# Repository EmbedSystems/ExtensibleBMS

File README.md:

# BMS
An extensible BMS with fast charging and battery pack scalability

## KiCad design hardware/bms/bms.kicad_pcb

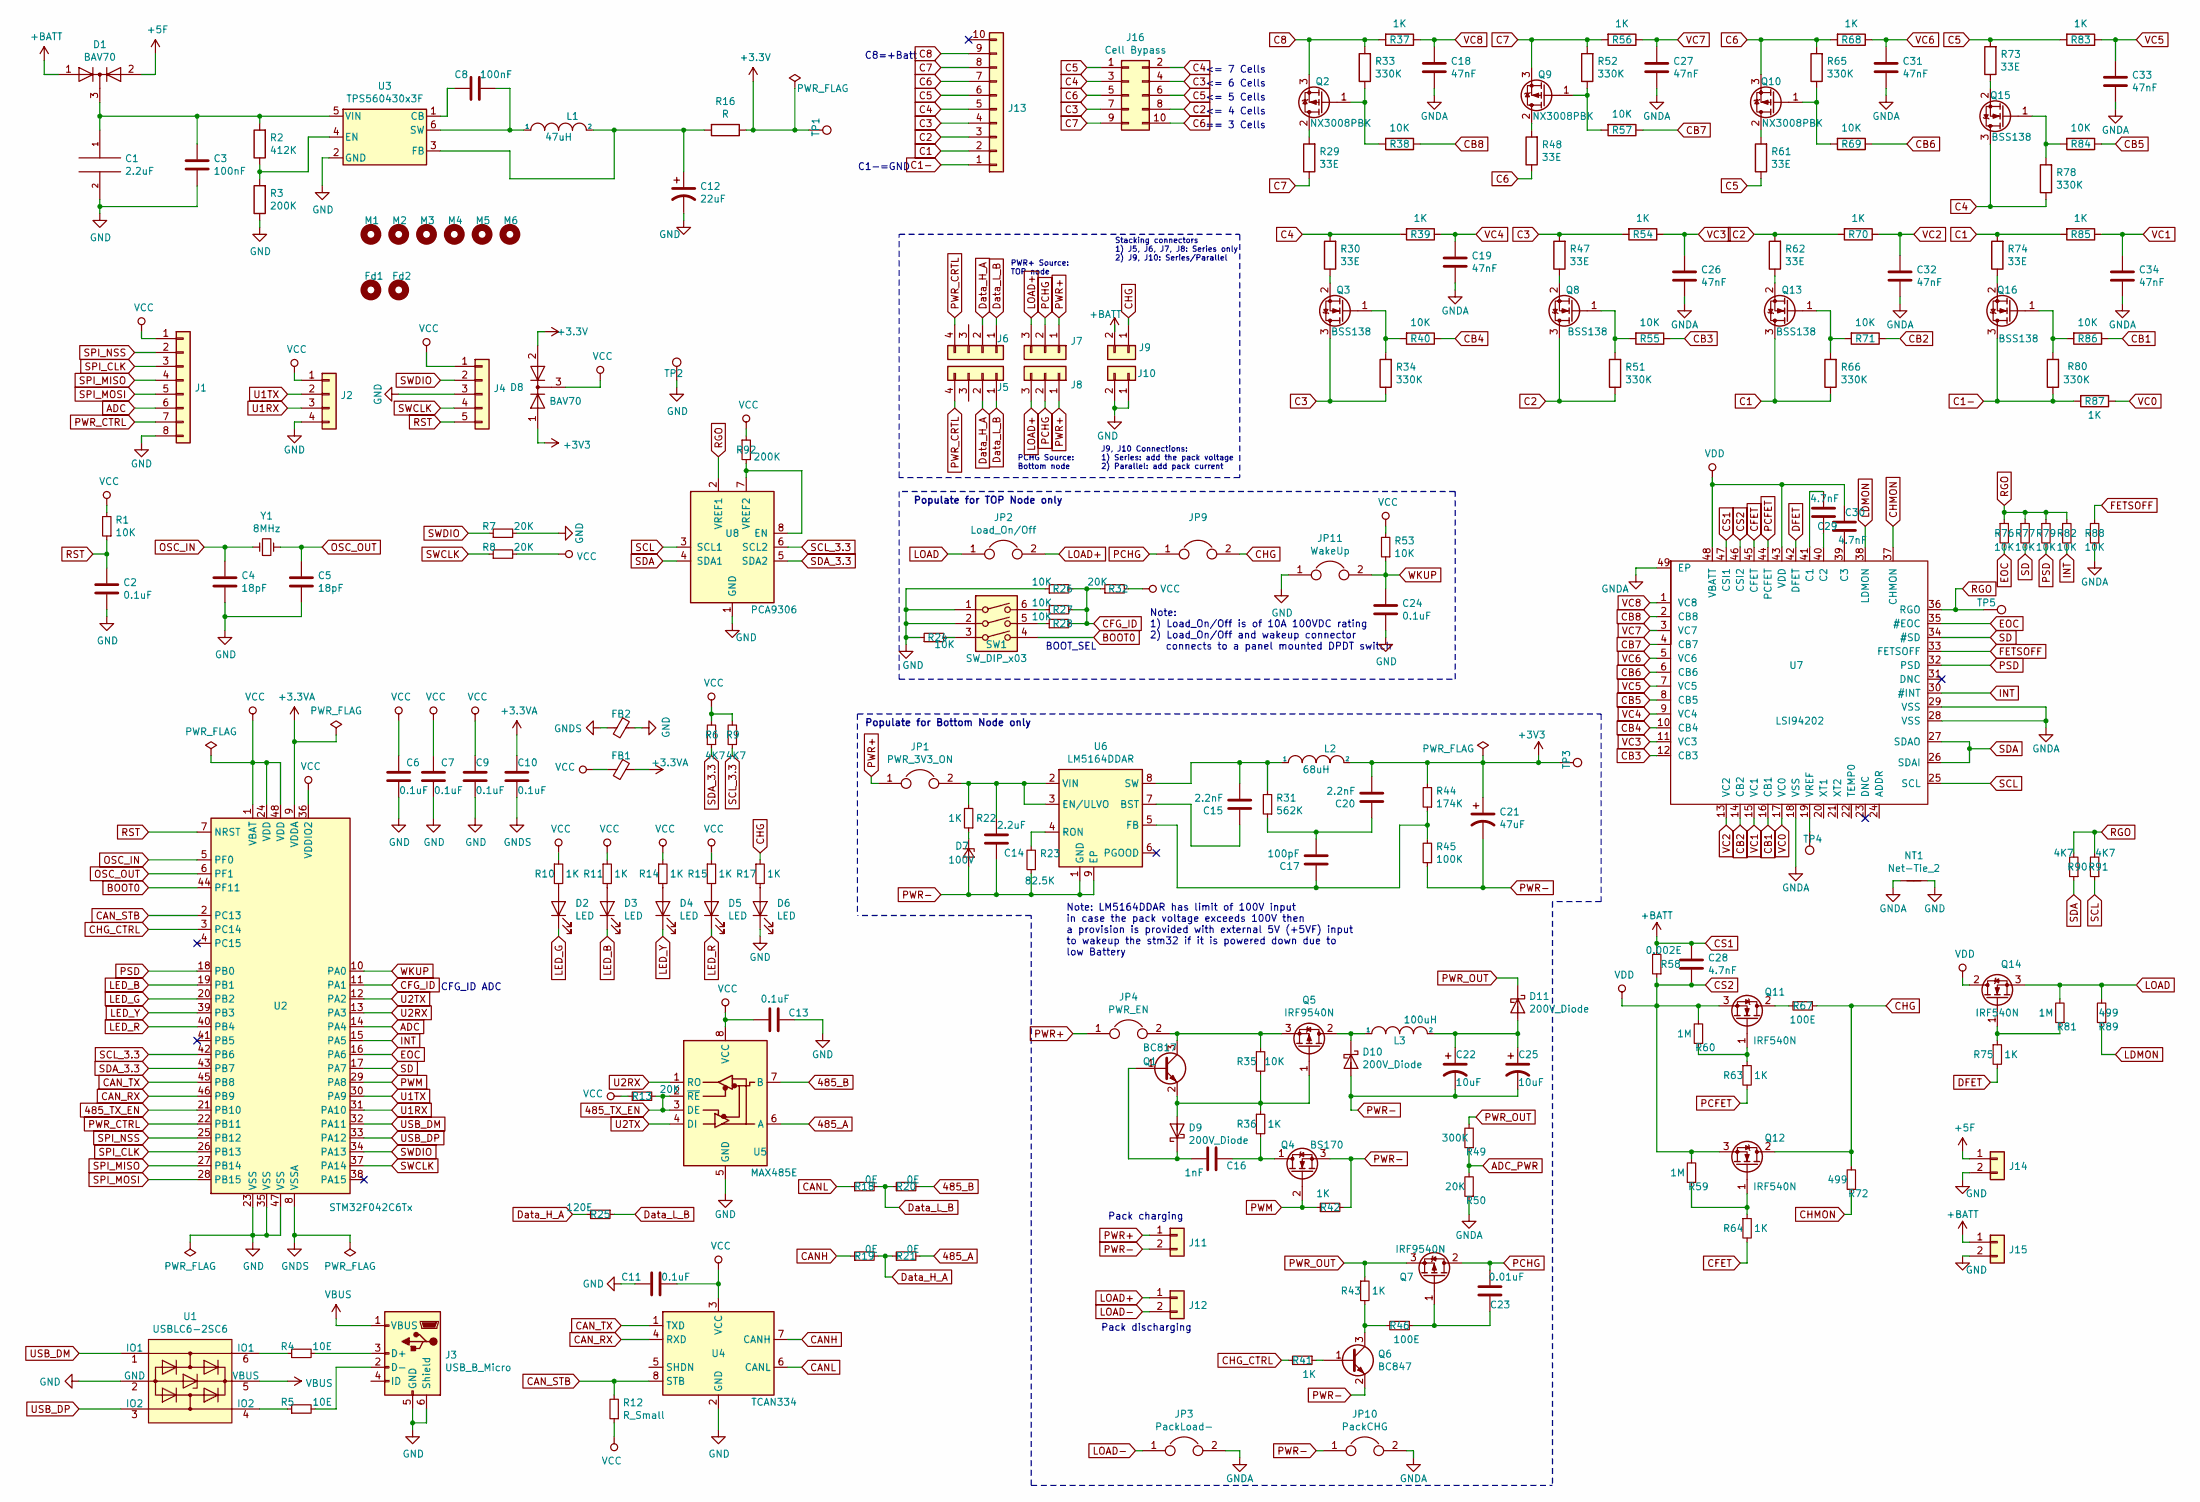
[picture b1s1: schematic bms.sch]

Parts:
C1: 2.2uF; C_1210_3225Metric_Pad1.42x2.65mm_HandSolder
C2, C6, C7, C9, C10, C11, C13, C24: 0.1uF; C_0603_1608Metric_Pad1.05x0.95mm_HandSolder
C3, C8: 100nF; C_0603_1608Metric_Pad1.05x0.95mm_HandSolder
C4, C5: 18pF; C_0603_1608Metric_Pad1.05x0.95mm_HandSolder
C12: 22uF; CP_EIA-3528-21_Kemet-B
C14: 2.2uF; C_0603_1608Metric_Pad1.05x0.95mm_HandSolder
C15, C20: 2.2nF; C_0603_1608Metric_Pad1.05x0.95mm_HandSolder
C16: 1nF; C_0603_1608Metric_Pad1.05x0.95mm_HandSolder
C17: 100pF; C_0603_1608Metric_Pad1.05x0.95mm_HandSolder
C18, C19, C26, C27, C31, C32, C33, C34: 47nF; C_0603_1608Metric_Pad1.05x0.95mm_HandSolder
C21: 47uF; CP_EIA-3528-21_Kemet-B
C22, C25: 10uF; CP_EIA-7132-28_AVX-C
C23: 0.01uF; C_1206_3216Metric_Pad1.42x1.75mm_HandSolder
C28, C29, C30: 4.7nF; C_0603_1608Metric_Pad1.05x0.95mm_HandSolder
D1, D8: BAV70; SOT-23
D2, D3, D4, D5, D6: LED; LED_0805_2012Metric
D7: 100V; D_MELF_Handsoldering
D9, D10, D11: 200V_Diode; D2PAK
FB1, FB2: Ferrite_Bead_Small; L_0805_2012Metric_Pad1.15x1.40mm_HandSolder
Fd1, Fd2: MountingHole; Fiducial_1mm_Mask2mm
J1: Conn_01x08; PinHeader_1x08_P1.00mm_Vertical
J2, J5, J6: Conn_01x04; Molex_KK-254_AE-6410-04A_1x04_P2.54mm_Vertical
J3: USB_B_Micro; USB_Micro-B_Molex-105017-0001
J4: Conn_01x05; Molex_KK-254_AE-6410-05A_1x05_P2.54mm_Vertical
J7, J8: Conn_01x03; TerminalBlock_bornier-3_P5.08mm
J9, J10, J11, J12: Conn_01x02; TerminalBlock_bornier-2_P5.08mm
J13: Conn_01x10; Molex_KK-254_AE-6410-10A_1x10_P2.54mm_Vertical
J14: Conn_01x02; PinSocket_1x02_P2.54mm_Vertical
J15: Conn_01x02; Molex_KK-396_A-41791-0002_1x02_P3.96mm_Vertical
J16: Cell Bypass; PinHeader_2x05_P2.54mm_Vertical
JP1: PWR_3V3_ON; PinHeader_1x02_P2.54mm_Vertical
JP2: Load_On/Off; PinHeader_1x02_P2.54mm_Vertical
JP3: PackLoad-; PinHeader_1x02_P2.54mm_Vertical
JP4: PWR_EN; PinHeader_1x02_P2.54mm_Vertical
JP9: Connector_PinHeader_2.54mm:PinHeader_1x02_P2.54mm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; PinHeader_1x02_P2.54mm_Vertical
JP10: PackCHG; PinHeader_1x02_P2.54mm_Vertical
JP11: WakeUp; PinHeader_1x02_P2.54mm_Vertical
L1: 47uH; L_Bourns_SRN6045TA
L2: 68uH; L_Bourns_SRN6045TA
L3: 100uH; L_Wuerth_HCI-1365
M1, M2, M3, M4, M5, M6: MountingHole; MountingHole_3.2mm_M3_Pad
NT1: Net-Tie_2; NetTie-2_THT_Pad1.0mm
Q1: BC817; SOT-23
Q2, Q9, Q10: NX3008PBK; SOT-23
Q3, Q8, Q13, Q15, Q16: BSS138; SOT-23
Q4: BS170; SOT-23W_Handsoldering
Q5, Q7: IRF9540N; TO-263-2
Q6: BC847; SOT-23
Q11, Q12, Q14: IRF540N; TO-263-2
R1, R24, R26, R27, R28, R35, R38, R40, R53, R55, R57, R69, R71, R76, R77, R79, R82, R84, R86, R88: 10K; R_0603_1608Metric_Pad1.05x0.95mm_HandSolder
R2: 412K; R_0603_1608Metric_Pad1.05x0.95mm_HandSolder
R3, R92: 200K; R_0603_1608Metric_Pad1.05x0.95mm_HandSolder
R4, R5: 10E; R_0603_1608Metric_Pad1.05x0.95mm_HandSolder
R6, R9, R90, R91: 4K7; R_0603_1608Metric_Pad1.05x0.95mm_HandSolder
R7, R8, R13, R32: 20K; R_0603_1608Metric_Pad1.05x0.95mm_HandSolder
R10, R11, R14, R15, R17, R36, R37, R39, R41, R42, R43, R54, R56, R63, R64, R68, R70, R75, R83, R85, R87: 1K; R_0603_1608Metric_Pad1.05x0.95mm_HandSolder
R12: R_Small; R_0603_1608Metric_Pad1.05x0.95mm_HandSolder
R16: R; R_1210_3225Metric_Pad1.42x2.65mm_HandSolder
R18, R19, R20, R21: 0E; R_0603_1608Metric_Pad1.05x0.95mm_HandSolder
R22: 1K; R_1206_3216Metric_Pad1.42x1.75mm_HandSolder
R23: 82.5K; R_0603_1608Metric_Pad1.05x0.95mm_HandSolder
R25: 120E; R_0603_1608Metric_Pad1.05x0.95mm_HandSolder
R29, R30, R47, R48, R61, R62, R73, R74: 33E; R_1210_3225Metric_Pad1.42x2.65mm_HandSolder
R31: 562K; R_0603_1608Metric_Pad1.05x0.95mm_HandSolder
R33, R34, R51, R52, R65, R66, R78, R80: 330K; R_0603_1608Metric_Pad1.05x0.95mm_HandSolder
R44: 174K; R_0603_1608Metric_Pad1.05x0.95mm_HandSolder
R45: 100K; R_0603_1608Metric_Pad1.05x0.95mm_HandSolder
R46, R67: 100E; R_0603_1608Metric_Pad1.05x0.95mm_HandSolder
R49: 300K; R_1206_3216Metric_Pad1.42x1.75mm_HandSolder
R50: 20K; R_1206_3216Metric_Pad1.42x1.75mm_HandSolder
R58: 0.002E; R_0603_1608Metric_Pad1.05x0.95mm_HandSolder
R59, R60, R81: 1M; R_0603_1608Metric_Pad1.05x0.95mm_HandSolder
R72, R89: 499; R_0603_1608Metric_Pad1.05x0.95mm_HandSolder
SW1: SW_DIP_x03; SW_DIP_SPSTx03_Slide_6.7x9.18mm_W6.73mm_P2.54mm_LowProfile_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
TP1, TP2, TP3, TP4, TP5: TestPoint; TestPoint_Pad_D1.5mm
U1: USBLC6-2SC6; SuperSOT-6
U2: STM32F042C6Tx; LQFP-48_7x7mm_P0.5mm
U3: TPS560430x3F; SOT-23-6
U4: TCAN334; SOIC-8_3.9x4.9mm_P1.27mm
U5: MAX485E; SOIC-8_3.9x4.9mm_P1.27mm
U6: LM5164DDAR; SOIC-8-1EP_3.9x4.9mm_P1.27mm_EP2.514x3.2mm_ThermalVias
U7: LSI94202; QFN-48-1EP_6x6mm_P0.4mm_EP4.66x4.66mm_ThermalVias
U8: PCA9306; SSOP-8_2.95x2.8mm_P0.65mm
Y1: 8MHz; Crystal_SMD_HC49-SD_HandSoldering

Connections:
485_A: R21.2, U5.6 (A)
485_B: R20.2, U5.7 (B)
485_TX_EN: R13.2, U2.21 (PB10), U5.2 (~RE), U5.3 (DE)
+3.3VA: C10.1, FB1.1, U2.9 (VDDA)
+5F: D1.2 (A), J14.1
ADC: J1.6, U2.14 (PA4)
ADC_PWR: R49.1, R50.2
BOOT0: SW1.4, U2.44 (PF11)
C1: J13.2, Q13.3 (D), R66.1, R74.2, R85.2
C1-: J13.1, Q16.3 (D), R80.1, R87.2
C2: J13.3, J16.8, Q8.3 (D), R51.1, R62.2, R70.2
C3: J13.4, J16.4, J16.7, Q3.3 (D), R34.1, R47.2, R54.2
C4: J13.5, J16.2, J16.3, Q15.3 (D), R30.2, R39.2, R78.1
C5: J13.6, J16.1, J16.6, R61.1, R73.2, R83.2
C6: J13.7, J16.5, J16.10, Q10.3 (S), R48.1, R65.2, R68.2
C7: J13.8, J16.9, Q9.3 (S), R29.1, R52.2, R56.2
C8: J13.9, Q2.3 (S), R33.2, R37.2
CANH: R19.1, U4.7 (CANH)
CANL: R18.1, U4.6 (CANL)
CAN_RX: U2.46 (PB9), U4.4 (RXD)
CAN_STB: R12.2, U2.2 (PC13), U4.8 (STB)
CAN_TX: U2.45 (PB8), U4.1 (TXD)
CB1: R86.1, U7.16 (CB1)
CB2: R71.1, U7.14 (CB2)
CB3: R55.1, U7.12 (CB3)
CB4: R40.1, U7.10 (CB4)
CB5: R84.1, U7.8 (CB5)
CB6: R69.1, U7.6 (CB6)
CB7: R57.1, U7.4 (CB7)
CB8: R38.1, U7.2 (CB8)
CFET: R64.2, U7.45 (CFET)
CFG_ID: R26.2, R27.2, R28.2, R32.1, U2.11 (PA1)
CHG: J9.1, JP9.2, Q12.2 (D), R17.1, R67.1, R72.2
CHG_CTRL: R41.2, U2.3 (PC14)
CHMON: R72.1, U7.37 (CHMON)
CS1: C28.1, D1.1 (A), J9.2, J15.1, R58.2, U7.47 (CSI1)
CS2: C28.2, C30.1, Q11.3 (S), Q12.3 (S), Q14.2 (D), R58.1, R59.2, R60.2, U7.43 (VDD), U7.46 (CSI2), U7.48 (VBATT)
DFET: R75.2, U7.42 (DFET)
Data_H_A: J5.2, J6.2, R19.2, R21.1, R25.2
Data_L_B: J5.1, J6.1, R18.2, R20.1, R25.1
EOC: R76.2, U2.16 (PA6), U7.35 (#EOC)
FETSOFF: R88.1, U7.33 (FETSOFF)
GND: C1.2, C2.2, C3.2, C4.2, C5.2, C6.2, C7.2, C9.2, C11.1, C12.2, C13.1, C24.2, D6.1 (K), FB2.1, J1.8, J2.4, J3.5 (GND), J3.6 (Shield), J4.3, J10.1, J10.2, J14.2, J15.2, JP11.1, NT1.2, R3.1, R7.2, R24.1, R26.1, SW1.1, SW1.2, TP2.1, U1.2 (GND), U2.23 (VSS), U2.35 (VSS), U2.47 (VSS), U3.2 (GND), U4.2 (GND), U5.5 (GND), U8.1 (GND)
GNDA: C18.2, C19.2, C26.2, C27.2, C31.2, C32.2, C33.2, C34.2, JP3.2, JP10.2, NT1.1, R50.1, R88.2, U7.18 (VSS), U7.28 (VSS), U7.29 (VSS), U7.49 (EP)
GNDS: C10.2, FB2.2, U2.8 (VSSA)
INT: R82.2, U2.15 (PA5), U7.30 (#INT)
LDMON: R89.1, U7.38 (LDMON)
LED_B: D3.1 (K), U2.19 (PB1)
LED_G: D2.1 (K), U2.20 (PB2)
LED_R: D5.1 (K), U2.40 (PB4)
LED_Y: D4.1 (K), U2.39 (PB3)
LOAD: JP2.1, Q14.3 (S), R81.2, R89.2
LOAD+: J7.3, J8.3, J12.1, JP2.2
LOAD-: J12.2, JP3.1
unnamed: C1.1, C3.1, D1.3 (K), R2.2, U3.5 (VIN)
unnamed: C8.1, L1.1, U3.6 (SW)
unnamed: C8.2, U3.1 (CB)
unnamed: C12.1, L1.2, R16.2, U3.3 (FB)
unnamed: C14.1, JP1.2, R22.2, U6.2 (VIN), U6.3 (EN/ULVO)
unnamed: C15.1, U6.7 (BST)
unnamed: C15.2, L2.1, R31.2, U6.8 (SW)
unnamed: C16.1, Q4.1 (D), R36.2
unnamed: C16.2, D9.4, Q1.1 (B)
unnamed: C17.1, R44.1, R45.2, U6.5 (FB)
unnamed: C17.2, C20.1, R31.1
unnamed: C22.1, C25.1, D11.1, D11.3, L3.2
unnamed: C23.1, Q7.1 (G), R46.1
unnamed: C29.1, U7.41 (C1)
unnamed: C29.2, U7.40 (C2)
unnamed: C30.2, U7.39 (C3)
unnamed: D2.2 (A), R10.2
unnamed: D3.2 (A), R11.2
unnamed: D4.2 (A), R14.2
unnamed: D5.2 (A), R15.2
unnamed: D6.2 (A), R17.2
unnamed: D7.1 (K), R22.1
unnamed: D9.1, D9.3, Q1.2 (E), Q5.1 (G), R35.2, R36.1
unnamed: D10.4, L3.1, Q5.2 (D)
unnamed: J3.2 (D-), R5.2
unnamed: J3.3 (D+), R4.2
unnamed: JP4.2, Q1.3 (C), Q5.3 (S), R35.1
unnamed: Q2.1 (G), R33.1, R38.2
unnamed: Q2.2 (D), R29.2
unnamed: Q3.1 (G), R34.2, R40.2
unnamed: Q3.2 (S), R30.1
unnamed: Q6.1 (B), R41.1
unnamed: Q6.3 (C), R43.2, R46.2
unnamed: Q8.1 (G), R51.2, R55.2
unnamed: Q8.2 (S), R47.1
unnamed: Q9.1 (G), R52.1, R57.2
unnamed: Q9.2 (D), R48.2
unnamed: Q10.1 (G), R65.1, R69.2
unnamed: Q10.2 (D), R61.2
unnamed: Q11.1 (G), R60.1, R63.1
unnamed: Q11.2 (D), R67.2
unnamed: Q12.1 (G), R59.1, R64.1
unnamed: Q13.1 (G), R66.2, R71.2
unnamed: Q13.2 (S), R62.1
unnamed: Q14.1 (G), R75.1, R81.1
unnamed: Q15.1 (G), R78.2, R84.2
unnamed: Q15.2 (S), R73.1
unnamed: Q16.1 (G), R80.2, R86.2
unnamed: Q16.2 (S), R74.1
unnamed: R2.1, R3.2, U3.4 (EN)
unnamed: R4.1, U1.6 (IO1)
unnamed: R5.1, U1.4 (IO2)
unnamed: R23.2, U6.4 (RON)
unnamed: R24.2, SW1.3
unnamed: R27.1, SW1.6
unnamed: R28.1, SW1.5
unnamed: R92.2, U8.7 (VREF2), U8.8 (EN)
unnamed: TP4.1, U7.19 (VREF)
OSC_IN: C4.1, U2.5 (PF0), Y1.1
OSC_OUT: C5.1, U2.6 (PF1), Y1.2
PCFET: R63.2, U7.44 (PCFET)
PCHG: C23.2, J7.2, J8.2, JP9.1, Q7.2 (D)
PSD: R79.2, U2.18 (PB0), U7.32 (PSD)
PWM: Q4.2 (G), R42.1, U2.29 (PA8)
PWR+: J7.1, J8.1, J11.1, JP1.1, JP4.1
PWR-: C14.2, C21.2, C22.2, C25.2, D7.2 (A), D10.1, D10.3, J11.2, JP10.1, Q4.3 (S), Q6.2 (E), R23.1, R42.2, R45.1, U6.1 (GND), U6.9 (EP)
PWR_CRTL: J5.4, J6.4
PWR_CTRL: J1.7, U2.22 (PB11)
PWR_OUT: D11.4, Q7.3 (S), R43.1, R49.2
RGO: R76.1, R77.1, R79.1, R82.1, R90.2, R91.2, TP5.1, U7.36 (RGO), U8.2 (VREF1)
RST: C2.1, J4.5, R1.1, U2.7 (NRST)
SCL: R91.1, U7.25 (SCL), U8.3 (SCL1)
SCL_3.3: R9.1, U2.42 (PB6), U8.6 (SCL2)
SD: R77.2, U2.17 (PA7), U7.34 (#SD)
SDA: R90.1, U7.26 (SDAI), U7.27 (SDAO), U8.4 (SDA1)
SDA_3.3: R6.1, U2.43 (PB7), U8.5 (SDA2)
SPI_CLK: J1.3, U2.26 (PB13)
SPI_MISO: J1.4, U2.27 (PB14)
SPI_MOSI: J1.5, U2.28 (PB15)
SPI_NSS: J1.2, U2.25 (PB12)
SWCLK: J4.4, R8.1, U2.37 (PA14)
SWDIO: J4.2, R7.1, U2.34 (PA13)
U1RX: J2.3, U2.31 (PA10)
U1TX: J2.2, U2.30 (PA9)
U2RX: U2.13 (PA3), U5.1 (RO)
U2TX: U2.12 (PA2), U5.4 (DI)
USB_DM: U1.1 (IO1), U2.32 (PA11)
USB_DP: U1.3 (IO2), U2.33 (PA12)
VBUS: J3.1 (VBUS), U1.5 (VBUS)
VC0: R87.1, U7.17 (VC0)
VC1: C34.1, R85.1, U7.15 (VC1)
VC2: C32.1, R70.1, U7.13 (VC2)
VC3: C26.1, R54.1, U7.11 (VC3)
VC4: C19.1, R39.1, U7.9 (VC4)
VC5: C33.1, R83.1, U7.7 (VC5)
VC6: C31.1, R68.1, U7.5 (VC6)
VC7: C27.1, R56.1, U7.3 (VC7)
VC8: C18.1, R37.1, U7.1 (VC8)
VCC: C6.1, C7.1, C9.1, C11.2, C13.2, D8.3 (K), FB1.2, J1.1, J2.1, J4.1, R1.2, R6.2, R8.2, R9.2, R10.1, R11.1, R12.1, R13.1, R14.1, R15.1, R32.2, R53.2, R92.1, U2.1 (VBAT), U2.24 (VDD), U2.36 (VDDIO2), U2.48 (VDD), U4.3 (VCC), U5.8 (VCC)
WKUP: C24.1, JP11.2, R53.1, U2.10 (PA0)

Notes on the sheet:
<= 7 Cells
<= 6 Cells
<= 5 Cells
<= 4 Cells
== 3 Cells
C8=+Batt
C1-=GND
PWR+ Source: TOP node
PCHG Source: Bottom node
Populate for TOP Node only
Pack charging
Pack discharging
Stacking connectors 1) J5, J6, J7, J8: Series only 2) J9, J10: Series/Parallel
Note: 1) Load_On/Off is of 10A 100VDC rating 2) Load_On/Off and wakeup connector connects to a panel mounted DPDT switch
CFG_ID ADC
Note: LM5164DDAR has limit of 100V input in case the pack voltage exceeds 100V then a provision is provided with external 5V (+5VF) input to wakeup the stm32 if it is powered down due to low Battery
Populate for Bottom Node only
BOOT_SEL
J9, J10 Connections: 1) Series: add the pack voltage 2) Parallel: add pack current

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
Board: 2 copper layers, 205 parts (30 on the bottom side), 155 nets, no tracks yet.

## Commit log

2020-02-13 Hardware building blocks
2020-02-13 Schematics update
2020-02-14 added packin and packout
2020-02-14 Updated power control
2020-02-14 added indication leds
2020-02-14 changed the charger power connection, need to fix the power delivery logic
2020-02-17 added switching logic for gnd and chg control
2020-02-18 updated charging logic and board to board connections
2020-02-19 added pack power management
2020-02-19 fixed power schematics
2020-02-19 Added On/Off control button
2020-02-20 added required provisions
2020-02-20 added bypass link for 3V3 power
2020-02-21 started adding footprint
2020-02-21 corrected and added footprints
2020-02-21 added datasheets
2020-02-21 fixed footprints
2020-02-24 added link to isolate charging power
2020-02-24 Changed connection to support series and parallel stacking
2020-02-24 created netlist
2020-02-25 fixed schematic errors, added isl94202 ref manual
2020-02-25 footprint corrections
2020-02-25 Added i2c level shifter
2020-02-26 Schematics and footprint corrections
2020-02-28 Started placement
2020-02-28 Changed placement
